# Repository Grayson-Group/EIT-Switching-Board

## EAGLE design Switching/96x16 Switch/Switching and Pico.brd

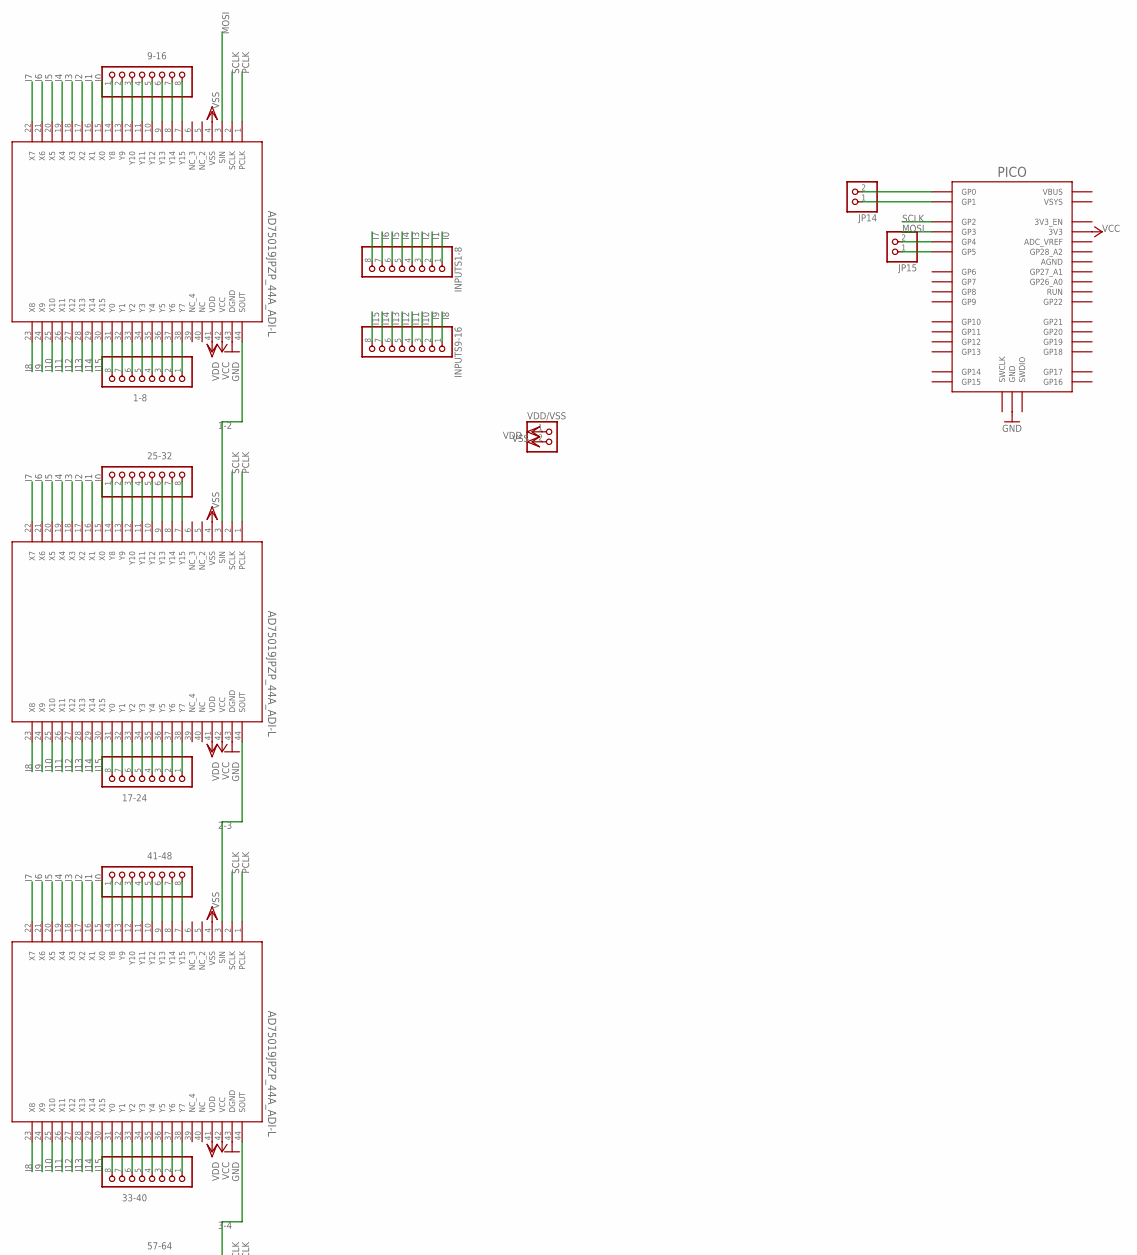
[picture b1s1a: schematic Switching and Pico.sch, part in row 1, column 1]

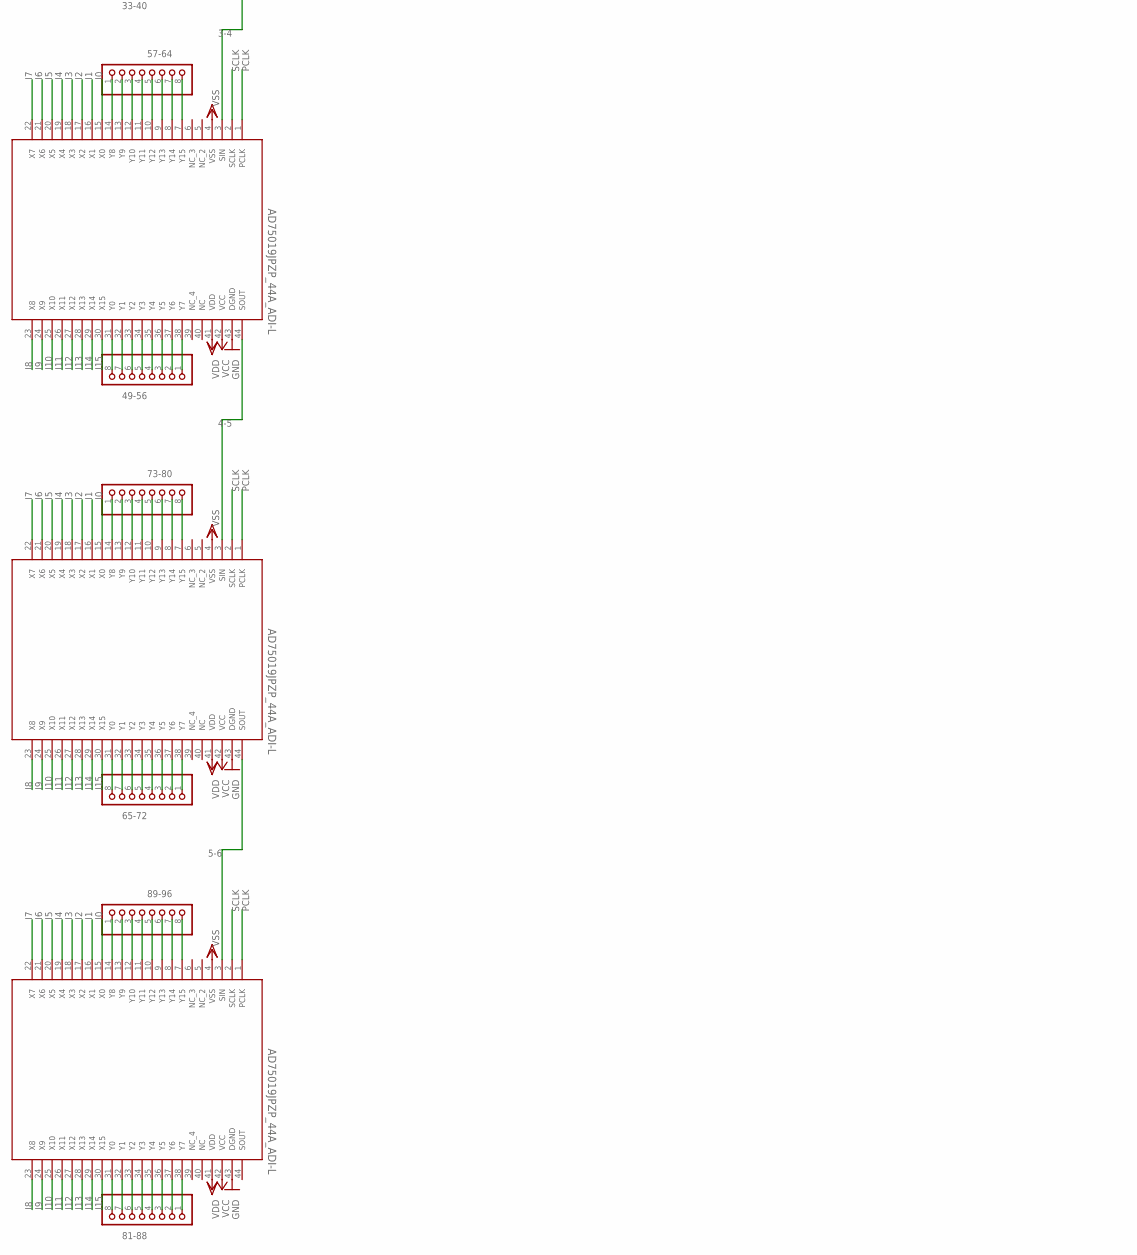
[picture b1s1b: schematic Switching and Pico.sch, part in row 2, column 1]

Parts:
1-8, 9-16, 17-24, 25-32, 33-40, 41-48, 49-56, 57-64, 65-72, 73-80, 81-88, 89-96: PINHD-1X8; 1X08
INPUTS1-8, INPUTS9-16: PINHD-1X8; 1X08
JP14, JP15: PINHD-1X2; 1X02
PICO: RPI_PICO-TH; RPI_PICO_TH
SWITCH1, SWITCH2, SWITCH3, SWITCH4, SWITCH5, SWITCH6: AD75019JPZP_44A_ADI-L; P_44A_ADI-L
VDD/VSS: PINHD-1X2; 1X02

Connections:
1-2: SWITCH1.44 (SOUT), SWITCH2.3 (SIN)
2-3: SWITCH2.44 (SOUT), SWITCH3.3 (SIN)
3-4: SWITCH3.44 (SOUT), SWITCH4.3 (SIN)
4-5: SWITCH4.44 (SOUT), SWITCH5.3 (SIN)
5-6: SWITCH5.44 (SOUT), SWITCH6.3 (SIN)
GND: PICO.GND@1 (GND), PICO.GND@2 (GND), PICO.GND@3 (GND), PICO.GND@4 (GND), PICO.GND@5 (GND), PICO.GND@6 (GND), PICO.GND@7 (GND), PICO.GND@8 (GND), SWITCH1.43 (DGND), SWITCH2.43 (DGND), SWITCH3.43 (DGND), SWITCH4.43 (DGND), SWITCH5.43 (DGND), SWITCH6.43 (DGND)
I0: INPUTS1-8.1, SWITCH1.15 (X0), SWITCH2.15 (X0), SWITCH3.15 (X0), SWITCH4.15 (X0), SWITCH5.15 (X0), SWITCH6.15 (X0)
I1: INPUTS1-8.2, SWITCH1.16 (X1), SWITCH2.16 (X1), SWITCH3.16 (X1), SWITCH4.16 (X1), SWITCH5.16 (X1), SWITCH6.16 (X1)
I2: INPUTS1-8.3, SWITCH1.17 (X2), SWITCH2.17 (X2), SWITCH3.17 (X2), SWITCH4.17 (X2), SWITCH5.17 (X2), SWITCH6.17 (X2)
I3: INPUTS1-8.4, SWITCH1.18 (X3), SWITCH2.18 (X3), SWITCH3.18 (X3), SWITCH4.18 (X3), SWITCH5.18 (X3), SWITCH6.18 (X3)
I4: INPUTS1-8.5, SWITCH1.19 (X4), SWITCH2.19 (X4), SWITCH3.19 (X4), SWITCH4.19 (X4), SWITCH5.19 (X4), SWITCH6.19 (X4)
I5: INPUTS1-8.6, SWITCH1.20 (X5), SWITCH2.20 (X5), SWITCH3.20 (X5), SWITCH4.20 (X5), SWITCH5.20 (X5), SWITCH6.20 (X5)
I6: INPUTS1-8.7, SWITCH1.21 (X6), SWITCH2.21 (X6), SWITCH3.21 (X6), SWITCH4.21 (X6), SWITCH5.21 (X6), SWITCH6.21 (X6)
I7: INPUTS1-8.8, SWITCH1.22 (X7), SWITCH2.22 (X7), SWITCH3.22 (X7), SWITCH4.22 (X7), SWITCH5.22 (X7), SWITCH6.22 (X7)
I8: INPUTS9-16.1, SWITCH1.23 (X8), SWITCH2.23 (X8), SWITCH3.23 (X8), SWITCH4.23 (X8), SWITCH5.23 (X8), SWITCH6.23 (X8)
I9: INPUTS9-16.2, SWITCH1.24 (X9), SWITCH2.24 (X9), SWITCH3.24 (X9), SWITCH4.24 (X9), SWITCH5.24 (X9), SWITCH6.24 (X9)
I10: INPUTS9-16.3, SWITCH1.25 (X10), SWITCH2.25 (X10), SWITCH3.25 (X10), SWITCH4.25 (X10), SWITCH5.25 (X10), SWITCH6.25 (X10)
I11: INPUTS9-16.4, SWITCH1.26 (X11), SWITCH2.26 (X11), SWITCH3.26 (X11), SWITCH4.26 (X11), SWITCH5.26 (X11), SWITCH6.26 (X11)
I12: INPUTS9-16.5, SWITCH1.27 (X12), SWITCH2.27 (X12), SWITCH3.27 (X12), SWITCH4.27 (X12), SWITCH5.27 (X12), SWITCH6.27 (X12)
I13: INPUTS9-16.6, SWITCH1.28 (X13), SWITCH2.28 (X13), SWITCH3.28 (X13), SWITCH4.28 (X13), SWITCH5.28 (X13), SWITCH6.28 (X13)
I14: INPUTS9-16.7, SWITCH1.29 (X14), SWITCH2.29 (X14), SWITCH3.29 (X14), SWITCH4.29 (X14), SWITCH5.29 (X14), SWITCH6.29 (X14)
I15: INPUTS9-16.8, SWITCH1.30 (X15), SWITCH2.30 (X15), SWITCH3.30 (X15), SWITCH4.30 (X15), SWITCH5.30 (X15), SWITCH6.30 (X15)
MOSI: PICO.GP3, SWITCH1.3 (SIN)
unnamed: 17-24.8, SWITCH2.31 (Y0)
unnamed: 17-24.7, SWITCH2.32 (Y1)
unnamed: 17-24.6, SWITCH2.33 (Y2)
unnamed: 17-24.5, SWITCH2.34 (Y3)
unnamed: 17-24.4, SWITCH2.35 (Y4)
unnamed: 17-24.3, SWITCH2.36 (Y5)
unnamed: 17-24.2, SWITCH2.37 (Y6)
unnamed: 17-24.1, SWITCH2.38 (Y7)
unnamed: 25-32.1, SWITCH2.14 (Y8)
unnamed: 25-32.2, SWITCH2.13 (Y9)
unnamed: 25-32.3, SWITCH2.12 (Y10)
unnamed: 25-32.4, SWITCH2.11 (Y11)
unnamed: 25-32.5, SWITCH2.10 (Y12)
unnamed: 25-32.6, SWITCH2.9 (Y13)
unnamed: 25-32.7, SWITCH2.8 (Y14)
unnamed: 1-8.8, SWITCH1.31 (Y0)
unnamed: 1-8.7, SWITCH1.32 (Y1)
unnamed: 1-8.6, SWITCH1.33 (Y2)
unnamed: 1-8.5, SWITCH1.34 (Y3)
unnamed: 1-8.4, SWITCH1.35 (Y4)
unnamed: 1-8.3, SWITCH1.36 (Y5)
unnamed: 1-8.2, SWITCH1.37 (Y6)
unnamed: 1-8.1, SWITCH1.38 (Y7)
unnamed: 9-16.1, SWITCH1.14 (Y8)
unnamed: 9-16.2, SWITCH1.13 (Y9)
unnamed: 9-16.3, SWITCH1.12 (Y10)
unnamed: 9-16.4, SWITCH1.11 (Y11)
unnamed: 9-16.5, SWITCH1.10 (Y12)
unnamed: 9-16.6, SWITCH1.9 (Y13)
unnamed: 9-16.7, SWITCH1.8 (Y14)
unnamed: 9-16.8, SWITCH1.7 (Y15)
unnamed: 25-32.8, SWITCH2.7 (Y15)
unnamed: 33-40.8, SWITCH3.31 (Y0)
unnamed: 33-40.7, SWITCH3.32 (Y1)
unnamed: 33-40.6, SWITCH3.33 (Y2)
unnamed: 33-40.5, SWITCH3.34 (Y3)
unnamed: 33-40.4, SWITCH3.35 (Y4)
unnamed: 33-40.3, SWITCH3.36 (Y5)
unnamed: 33-40.2, SWITCH3.37 (Y6)
unnamed: 33-40.1, SWITCH3.38 (Y7)
unnamed: 41-48.1, SWITCH3.14 (Y8)
unnamed: 41-48.2, SWITCH3.13 (Y9)
unnamed: 41-48.3, SWITCH3.12 (Y10)
unnamed: 41-48.4, SWITCH3.11 (Y11)
unnamed: 41-48.5, SWITCH3.10 (Y12)
unnamed: 41-48.6, SWITCH3.9 (Y13)
unnamed: 41-48.7, SWITCH3.8 (Y14)
unnamed: 41-48.8, SWITCH3.7 (Y15)
unnamed: 49-56.8, SWITCH4.31 (Y0)
unnamed: 49-56.7, SWITCH4.32 (Y1)
unnamed: 49-56.6, SWITCH4.33 (Y2)
unnamed: 49-56.5, SWITCH4.34 (Y3)
unnamed: 49-56.4, SWITCH4.35 (Y4)
unnamed: 49-56.3, SWITCH4.36 (Y5)
unnamed: 49-56.2, SWITCH4.37 (Y6)
unnamed: 49-56.1, SWITCH4.38 (Y7)
unnamed: 57-64.1, SWITCH4.14 (Y8)
unnamed: 57-64.2, SWITCH4.13 (Y9)
unnamed: 57-64.3, SWITCH4.12 (Y10)
unnamed: 57-64.4, SWITCH4.11 (Y11)
unnamed: 57-64.5, SWITCH4.10 (Y12)
unnamed: 57-64.6, SWITCH4.9 (Y13)
unnamed: 57-64.7, SWITCH4.8 (Y14)
unnamed: 57-64.8, SWITCH4.7 (Y15)
unnamed: 65-72.8, SWITCH5.31 (Y0)
unnamed: 65-72.7, SWITCH5.32 (Y1)
unnamed: 65-72.6, SWITCH5.33 (Y2)
unnamed: 65-72.5, SWITCH5.34 (Y3)
unnamed: 65-72.4, SWITCH5.35 (Y4)
unnamed: 65-72.3, SWITCH5.36 (Y5)
unnamed: 65-72.2, SWITCH5.37 (Y6)
unnamed: 65-72.1, SWITCH5.38 (Y7)
unnamed: 73-80.1, SWITCH5.14 (Y8)
unnamed: 73-80.2, SWITCH5.13 (Y9)
unnamed: 73-80.3, SWITCH5.12 (Y10)
unnamed: 73-80.4, SWITCH5.11 (Y11)
unnamed: 73-80.5, SWITCH5.10 (Y12)
unnamed: 73-80.6, SWITCH5.9 (Y13)
unnamed: 73-80.7, SWITCH5.8 (Y14)
unnamed: 73-80.8, SWITCH5.7 (Y15)
unnamed: JP14.2, PICO.GP0
unnamed: 81-88.8, SWITCH6.31 (Y0)
unnamed: 81-88.7, SWITCH6.32 (Y1)
unnamed: 81-88.6, SWITCH6.33 (Y2)
unnamed: 81-88.5, SWITCH6.34 (Y3)
unnamed: 81-88.4, SWITCH6.35 (Y4)
unnamed: 81-88.3, SWITCH6.36 (Y5)
unnamed: 81-88.2, SWITCH6.37 (Y6)
unnamed: 81-88.1, SWITCH6.38 (Y7)
unnamed: 89-96.1, SWITCH6.14 (Y8)
unnamed: 89-96.2, SWITCH6.13 (Y9)
unnamed: 89-96.3, SWITCH6.12 (Y10)
unnamed: 89-96.4, SWITCH6.11 (Y11)
unnamed: 89-96.5, SWITCH6.10 (Y12)
unnamed: 89-96.6, SWITCH6.9 (Y13)
unnamed: 89-96.7, SWITCH6.8 (Y14)
unnamed: 89-96.8, SWITCH6.7 (Y15)
unnamed: JP14.1, PICO.GP1
unnamed: JP15.2, PICO.GP4
unnamed: JP15.1, PICO.GP5
PCLK: SWITCH1.1 (PCLK), SWITCH2.1 (PCLK), SWITCH3.1 (PCLK), SWITCH4.1 (PCLK), SWITCH5.1 (PCLK), SWITCH6.1 (PCLK)
SCLK: PICO.GP2, SWITCH1.2 (SCLK), SWITCH2.2 (SCLK), SWITCH3.2 (SCLK), SWITCH4.2 (SCLK), SWITCH5.2 (SCLK), SWITCH6.2 (SCLK)
VCC: PICO.3V3, SWITCH1.42 (VCC), SWITCH2.42 (VCC), SWITCH3.42 (VCC), SWITCH4.42 (VCC), SWITCH5.42 (VCC), SWITCH6.42 (VCC)
VDD: SWITCH1.41 (VDD), SWITCH2.41 (VDD), SWITCH3.41 (VDD), SWITCH4.41 (VDD), SWITCH5.41 (VDD), SWITCH6.41 (VDD), VDD/VSS.1
VSS: SWITCH1.4 (VSS), SWITCH2.4 (VSS), SWITCH3.4 (VSS), SWITCH4.4 (VSS), SWITCH5.4 (VSS), SWITCH6.4 (VSS), VDD/VSS.2

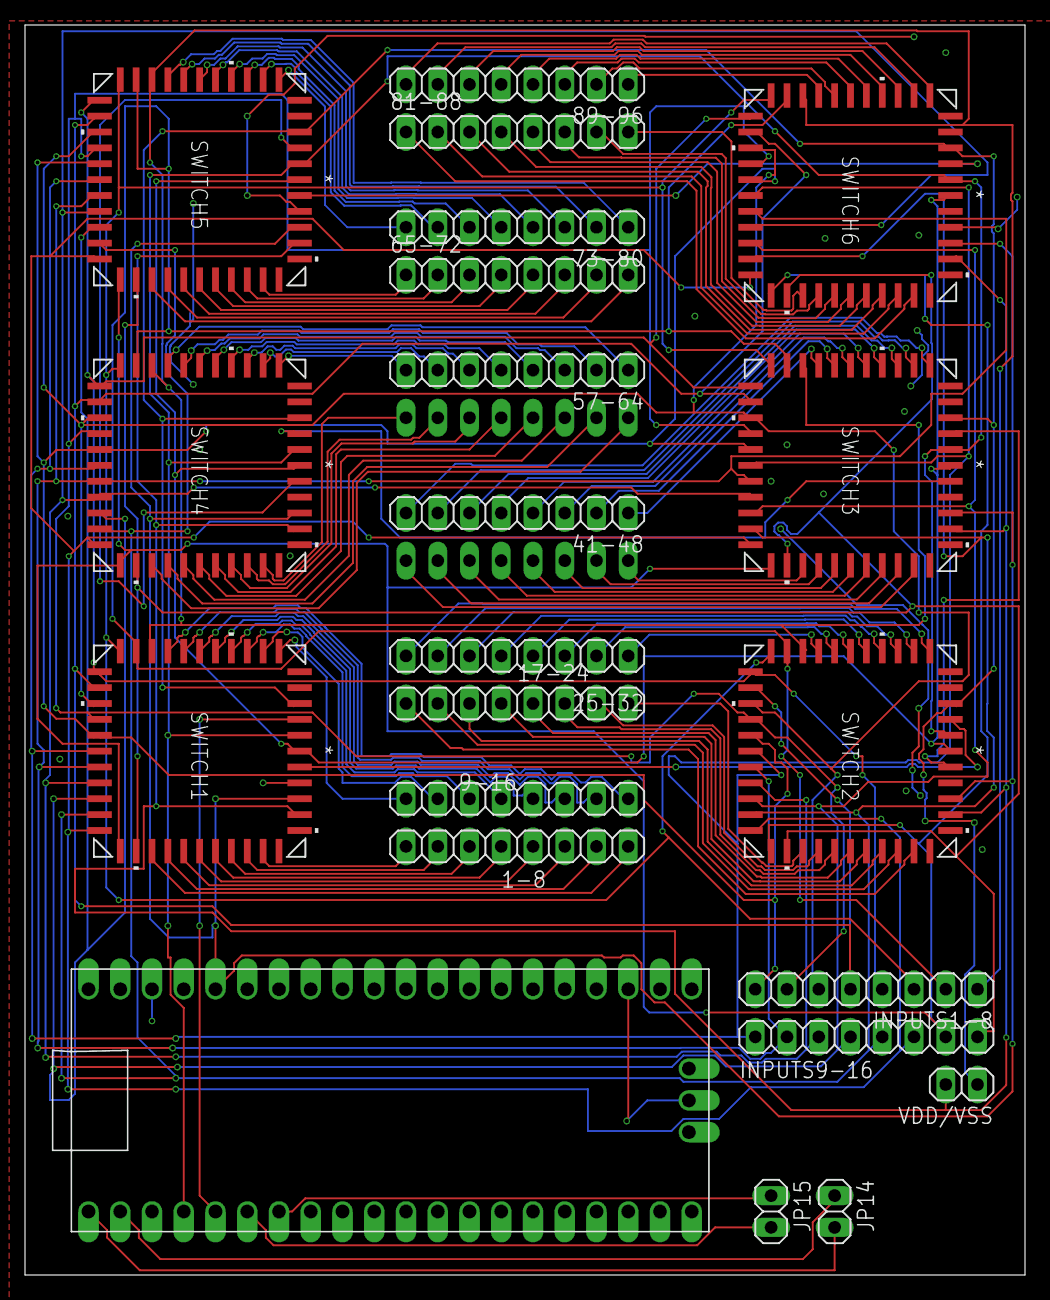
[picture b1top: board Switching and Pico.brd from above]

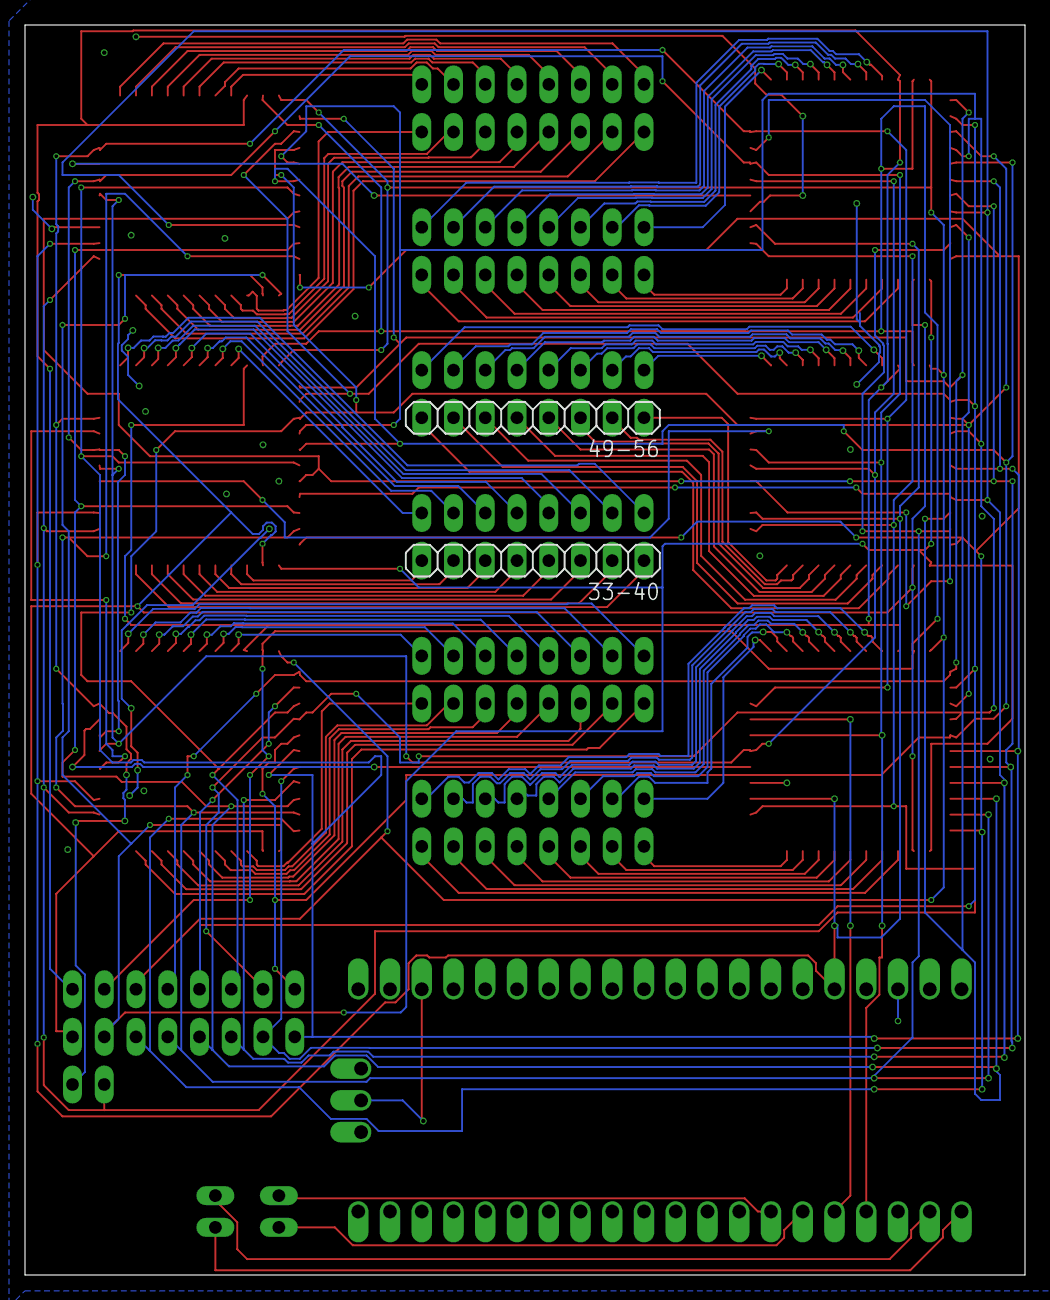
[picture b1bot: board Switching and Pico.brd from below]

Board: 2 copper layers, 80.0 x 100.0 mm, 24 parts (2 on the bottom side), 128 nets.

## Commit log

2024-06-21 pico and switch
    base board with pico controller and switching ICs. inputs and outputs as headers

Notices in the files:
parts and their libraries:
COPYRIGHT: Copyright (C) 2024 Ultra Librarian. All rights reserved.
